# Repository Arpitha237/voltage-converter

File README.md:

## Voltage Regulator Circuit 

This document explains the components, working, and usage of the provided voltage regulator circuit diagram.

**Components:**

* **J1 (Conn\_01x02\_Pin):** This is a 2-pin connector that serves as the input for the circuit. It is labeled with "input1" and "input2". This suggests that the input might be an AC voltage source, as it needs to be rectified before regulation.

* **D1, D2, D3, D4 (Diodes):** These four diodes are arranged in a bridge rectifier configuration. A bridge rectifier converts an AC input voltage into a pulsating DC voltage.
    * During one half-cycle of the AC input, diodes D1 and D4 will be forward-biased, allowing current to flow.
    * During the other half-cycle, diodes D2 and D3 will be forward-biased, again allowing current to flow in the same direction through the rest of the circuit.
    * The output of the bridge rectifier is a DC voltage that varies in magnitude.

* **C1 (Capacitor):** This is a filter capacitor connected in parallel with the output of the bridge rectifier.
    * It smooths out the pulsating DC voltage from the rectifier by charging up during the peaks of the voltage waveform and discharging during the troughs.
    * This results in a more stable DC voltage as input to the voltage regulator.

* **U1 (L7805):** This is a three-terminal positive voltage regulator integrated circuit. The "L7805" indicates that it is designed to provide a fixed output voltage of +5 volts. It has three pins:
    * **Pin 1 (IN):** This is the input pin where the unregulated DC voltage (smoothed by capacitor C1) is applied.
    * **Pin 2 (GND):** This is the ground pin, which is connected to the common ground of the circuit.
    * **Pin 3 (OUT):** This is the output pin, which provides the regulated +5V DC voltage.

* **R1 (R):** This is a current-limiting resistor connected in series with the LED (D5).
    * It limits the amount of current flowing through the LED to prevent it from being damaged due to excessive current. The value of this resistor will determine the brightness of the LED.

* **D5 (LED):** This is a Light Emitting Diode.
    * It is used as an indicator to show that the circuit is powered and the output voltage is present. When current flows through it, it will emit light.

* **PWR\_FLAG:** These are power flags indicating the positive voltage rail after the rectifier and regulator.

* **GND:** This symbol represents the ground connection, which is the common reference point for all voltages in the circuit.

**Working:**

1.  **AC Input:** An AC voltage is applied to the input connector J1.

2.  **Rectification:** The bridge rectifier (D1, D2, D3, D4) converts the AC input voltage into a pulsating DC voltage. Regardless of the polarity of the AC input, the current flows in the same direction through the output of the rectifier.

3.  **Filtering:** The filter capacitor C1 smooths out the pulsating DC voltage from the rectifier. It charges when the rectifier output voltage is high and discharges when it is low, reducing the voltage ripple and providing a more stable, albeit still unregulated, DC voltage to the input of the voltage regulator (U1).

4.  **Voltage Regulation:** The L7805 voltage regulator (U1) takes the unregulated DC input voltage and maintains a constant +5V DC output voltage, regardless of variations in the input voltage (within its specified operating range) or changes in the load current (up to its current rating).

5.  **Current Limiting:** The resistor R1 limits the current flowing through the LED (D5).

6.  **Indication:** The LED (D5) lights up when the regulated +5V output is available, providing a visual indication that the circuit is working.

**Usage of the Circuit:**

This type of voltage regulator circuit, providing a stable +5V output, has numerous applications in electronics, including:

* **Powering Microcontrollers and Logic Circuits:** Many microcontrollers (like Arduino), digital logic ICs (TTL, CMOS), and other low-power electronic components require a stable +5V power supply to operate correctly. This circuit can provide that regulated voltage.

* **Powering Sensors and Actuators:** Some sensors and small actuators operate at +5V. This circuit can be used to power them reliably.

* **Creating a Basic Bench Power Supply:** This circuit can be a fundamental building block for a simple bench power supply for hobbyists and electronics enthusiasts. By adding output terminals, it can provide a fixed +5V source for testing and prototyping.

* **Charging Low-Power Devices:** With appropriate current limiting, this +5V output can be used to charge small batteries or power devices that are charged via a 5V source (though more sophisticated charging circuitry might be needed for proper battery management).

* **Educational Purposes:** This is a common and straightforward circuit used in electronics education to demonstrate the principles of AC rectification, DC filtering, and linear voltage regulation.

* **As a Subsystem in Larger Electronic Devices:** This type of regulation is often integrated within larger electronic devices to provide a stable +5V rail for internal circuitry.

**In essence, this circuit is used whenever a stable and reliable +5V DC power source is required from an AC input.** The simplicity and robustness of the L7805 regulator make this a common and widely used circuit in various electronic applications.

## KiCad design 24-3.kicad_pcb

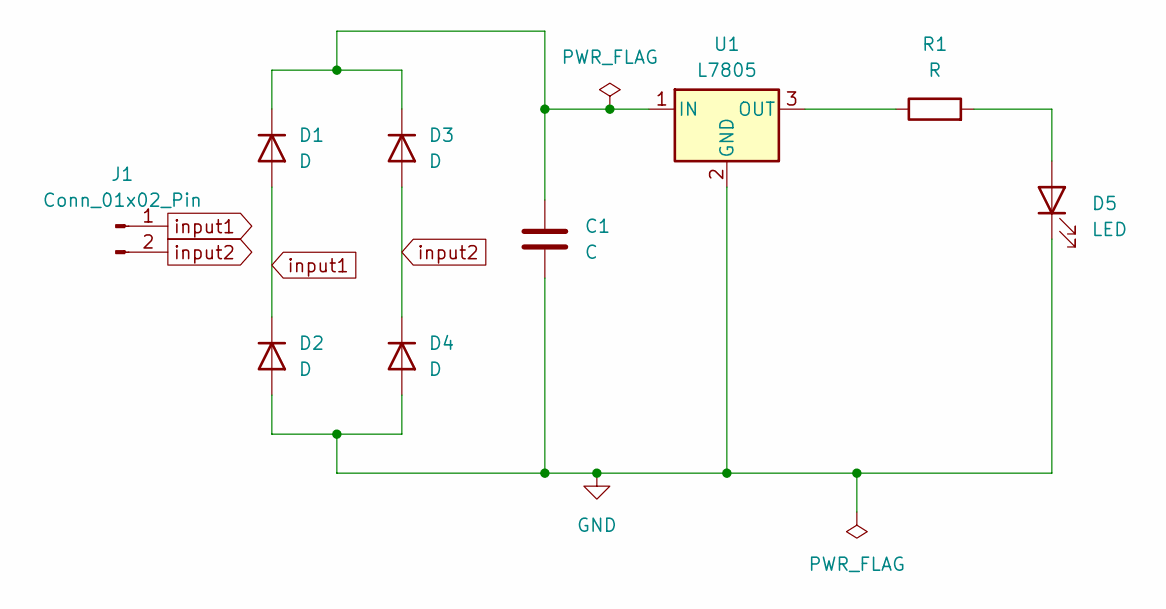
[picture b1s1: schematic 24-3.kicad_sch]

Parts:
C1: C; C_Radial_D6.3mm_H11.0mm_P2.50mm
D1, D2, D3, D4: D; D_5W_P10.16mm_Horizontal
D5: LED; LED_D5.0mm
J1: Conn_01x02_Pin; TerminalBlock_bornier-2_P5.08mm
R1: R; R_Axial_DIN0207_L6.3mm_D2.5mm_P2.54mm_Vertical
U1: L7805; TO-220-3_Vertical

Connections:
GND: C1.2, D2.2 (A), D4.2 (A), D5.1 (K), U1.2 (GND)
unnamed: C1.1, D1.1 (K), D3.1 (K), U1.1 (IN)
unnamed: D5.2 (A), R1.2
unnamed: R1.1, U1.3 (OUT)
input1: D1.2 (A), D2.1 (K), J1.1
input2: D3.2 (A), D4.1 (K), J1.2

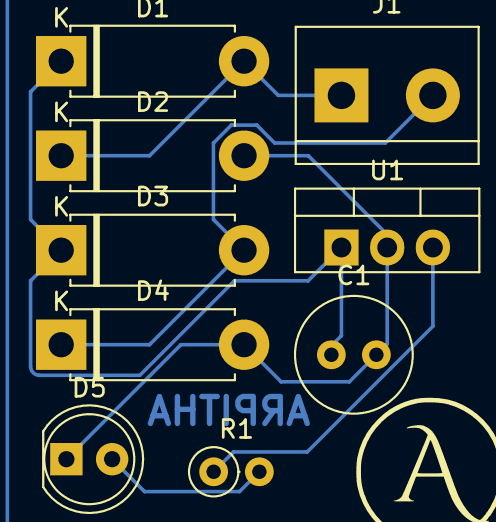
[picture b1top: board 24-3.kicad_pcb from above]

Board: 2 copper layers, 9 parts (0 on the bottom side), 6 nets.

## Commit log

2025-04-29 voltage coverter circuit is designed
